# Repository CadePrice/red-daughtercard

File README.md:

# teensy4.1-daughtercard

* Goal: Connect GigaPCB female connector (XG4H-5031) onto a Teensy 4.1 daughtercard.
* Solution: Use a male connector (XG4A-5034) to link GigaPCB to Teensy 4.1 MCU.

**ALL PLANNING INFORMATION AND PIN WORKS CAN BE FOUND HERE: https://docs.google.com/spreadsheets/d/1IKXbfIiIrP6nyM8Mc0eolMKgb26c2Qc9dl-_x0jVvCI/edit?usp=sharing**

Revisions after Design Review #1 (6/11)
* Added a 3v3 LED to indicate good board connection
* Made TX+/TX- and RX+/RX- differential pairs with matched lengths
* Added GND vias across the board
* Made it a four layer board (signals -> ground -> power -> signals)

Contains the daughtercard housing the Teensy4.1 MCU used for the GIGAPCB architecture for Texas A&amp;M Rocket Engine Design. An Standard Operating Procedure (SOP) will be provided for assembly/use instructions.

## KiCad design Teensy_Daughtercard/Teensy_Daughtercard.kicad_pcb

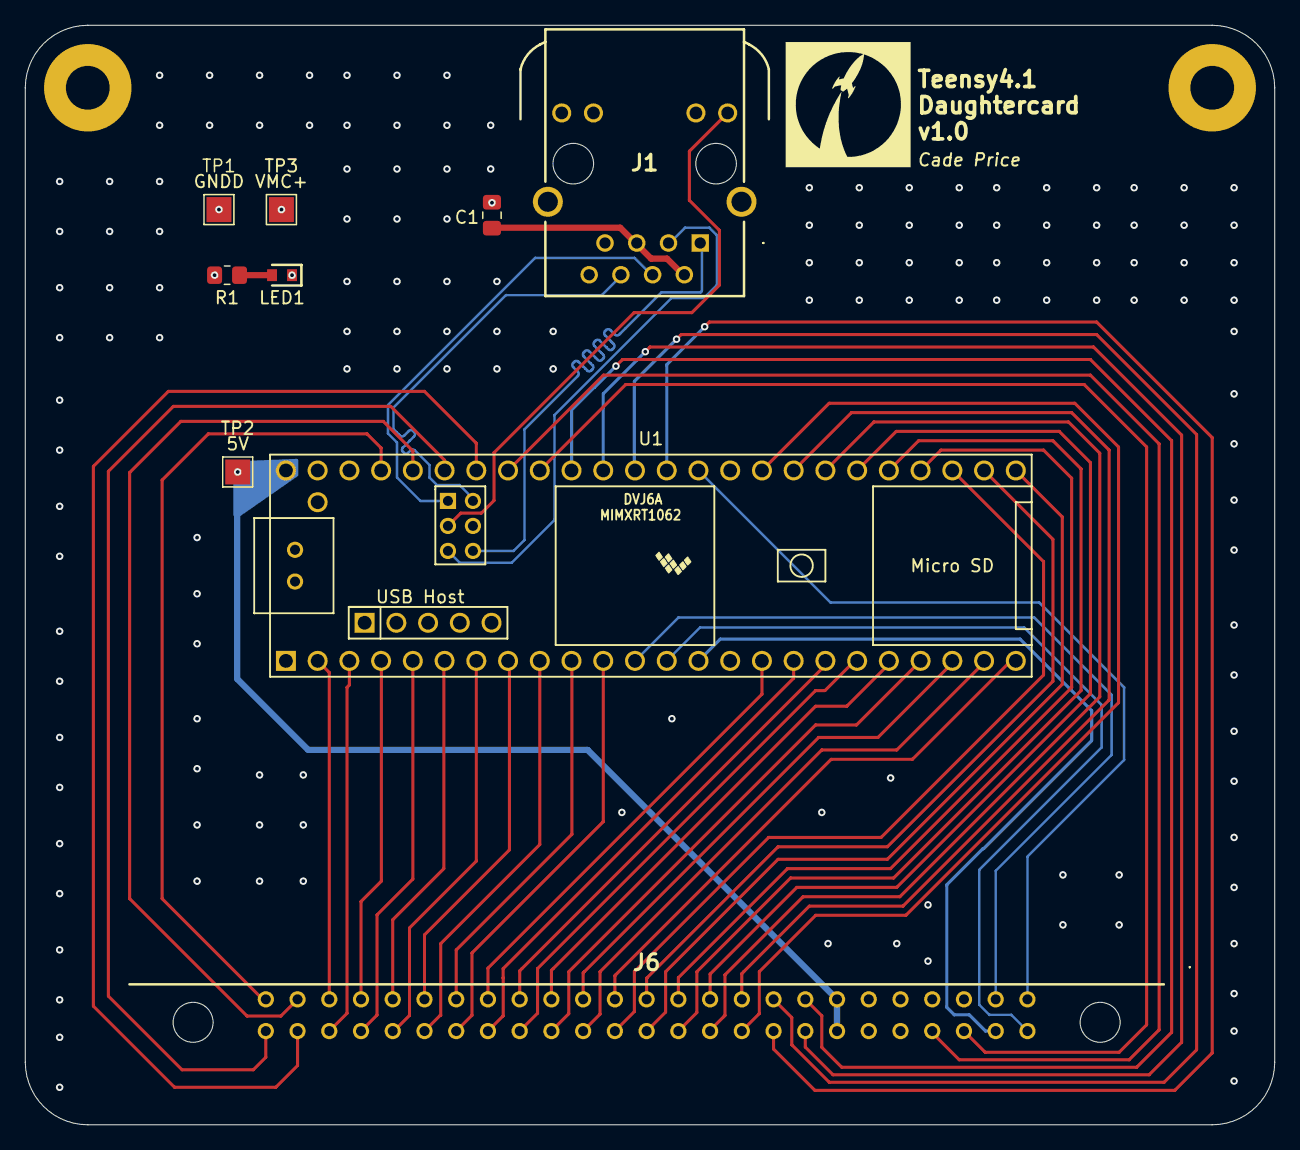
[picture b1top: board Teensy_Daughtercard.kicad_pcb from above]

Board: 4 copper layers, 100.0 x 88.0 mm, 11 parts (0 on the bottom side), 52 nets.

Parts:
C1: 0.1uF; C_0805_2012Metric_Pad1.18x1.45mm_HandSolder
H1, H2: MH; MountingHole_3.5mm_Pad
J1: 1664073
J6: XG4A-5034; XG4A5034
LED1: LTST-C190YKT; LEDC1608X90N
R1: 1000; R_0805_2012Metric_Pad1.20x1.40mm_HandSolder
TP1: GND; TestPoint_Pad_2.0x2.0mm
TP2: 5V; TestPoint_Pad_2.0x2.0mm
TP3: VMC+; TestPoint_Pad_2.0x2.0mm
U1: Teensy4.1; Teensy41

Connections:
+5V: J6.19, J6.44, TP2.1 (1_1), U1.48 (VIN)
/CS1: J6.49, U1.12 (10_CS_MQSR)
/DIR1: J6.37, U1.24 (32_OUT1B)
/DIR2: J6.16, U1.33 (41_A17)
/DIR3: J6.40, U1.30 (38_CS1_IN1)
/DIR4: J6.13, U1.25 (33_MCLK2)
/ENA1: J6.12, U1.27 (35_TX8)
/ENA2: J6.42, U1.37 (15_A1_RX3_SPDIF_IN)
/ENA3: J6.15, U1.31 (39_MISO1_OUT1A)
/ENA4: J6.39, U1.28 (36_CS)
/ETH_LED: J1.P11 (A_GREEN), U1.61 (LED)
/ETH_RX+: J1.P4 (RD+), U1.60 (R+)
/ETH_RX-: J1.P6 (RD-), U1.65 (R-)
/ETH_TX+: J1.P1 (TD+), U1.63 (T+)
/ETH_TX-: J1.P3 (TD-), U1.62 (T-)
/GPIO1: J6.28, U1.2 (0_RX1_CRX2_CS1)
/GPIO2: J6.29, U1.4 (2_OUT2)
/GPIO3: J6.30, U1.6 (4_BCLK2)
/GPIO4: J6.31, U1.8 (6_OUT1D)
/Imon PS1: J6.26, U1.45 (23_A9_CRX1_MCLK1)
/Imon PS2: J6.27, U1.44 (22_A8_CTX1)
/PUL1: J6.38, U1.26 (34_RX8)
/PUL2: J6.17, U1.36 (14_A0_TX3_SPDIF_OUT)
/PUL3: J6.41, U1.32 (40_A16)
/PUL4: J6.14, U1.29 (37_CS)
/RELAY1: J6.11, U1.23 (31_CTX3)
/RELAY2: J6.36, U1.22 (30_CRX3)
/RELAY3: J6.10, U1.21 (29_TX7)
/RELAY4: J6.35, U1.20 (28_RX7)
/RELAY5: J6.9, U1.19 (27_A13_SCK1)
/RELAY6: J6.34, U1.18 (26_A12_MOSI1)
/RELAY7: J6.33, U1.16 (24_A10_TX6_SCL2)
/RELAY8: J6.8, U1.17 (25_A11_RX6_SDA2)
/RELAY9: J6.7, U1.11 (9_OUT1C)
/RELAY10: J6.32, U1.10 (8_TX2_IN1)
/RELAY11: J6.6, U1.9 (7_RX2_OUT1A)
/RELAY12: J6.5, U1.7 (5_IN2)
/RELAY13: J6.4, U1.5 (3_LRCLK2)
/RELAY14: J6.3, U1.3 (1_TX1_CTX2_MISO1)
/RELAY15: J6.1, U1.43 (21_A7_RX5_BCLK1)
/RELAY16: J6.2, U1.42 (20_A6_TX5_LRCLK1)
/SCLK1: J6.50, U1.35 (13_SCK_LED)
/SCLLC: J6.18, U1.38 (16_A2_RX4_SCL1)
/SCLTC: J6.22, U1.41 (19_A5_SCL)
/SDALC: J6.43, U1.39 (17_A3_TX4_SDA1)
/SDATC: J6.23, U1.40 (18_A4_SDA)
/SDI1: J6.25, U1.13 (11_MOSI_CTX1)
/SDO1: J6.24, U1.14 (12_MISO_MQSL)
GNDD: C1.1, H1.1 (1_1), H2.1 (1_1), J1.P8 (CHS_GROUND), J1.P12 (K_GREEN), J6.21, J6.46, LED1.1 (K), TP1.1 (1_1), U1.1 (GND), U1.34 (GND), U1.47 (GND), U1.64 (GND)
unnamed: C1.2, J1.P2 (TCT), J1.P5 (RCT)
unnamed: LED1.2 (A), R1.1
VMC+: J6.20, J6.45, R1.2, TP3.1 (1_1), U1.15 (3V3), U1.46 (3V3)

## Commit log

2026-06-10 WIP 6/9/26
2026-06-11 First draft complete
2026-06-11 First revision 6/11
2026-06-18 Replaced Magjack
2026-06-20 Final changes
2026-06-20 Removed sop from directory
